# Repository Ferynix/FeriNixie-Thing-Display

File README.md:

# FeriNixie Thing Display
 A nixie tube display for furries ;3

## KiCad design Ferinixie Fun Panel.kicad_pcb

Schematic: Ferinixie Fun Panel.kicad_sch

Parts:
C1, C2: 1uF; C_Radial_D5.0mm_H5.0mm_P2.00mm
C5, C6, C7, C8: 100nF; C_0402_1005Metric
D1: MB6S; TO-269AA
NE1, NE2, NE3, NE4, NE5, NE6, NE7, NE8, NE9, NE10, NE11, NE12, NE13, NE14, NE15, NE16, NE17, NE18: INS-1
NIX1, NIX2, NIX3, NIX4, NIX5, NIX6, NIX7, NIX8, NIX9, NIX10, NIX11, NIX12, NIX13, NIX14, NIX15: IN-15A; IN-15A Stepped
PS1: IRM-05-5; Converter_ACDC_MeanWell_IRM-05-xx_THT
Q1, Q2, Q3, Q4, Q5, Q6, Q7, Q8, Q9, Q10, Q11, Q12, Q13, Q14, Q15, Q16, Q17, Q18, Q19, Q20, Q21, Q22, Q23, Q24, Q25, Q26, Q27, Q28, Q29, Q30, Q31, Q32, Q33, Q34, Q35, Q36, Q37, Q38, Q39, Q40, Q41, Q42, Q43, Q44, Q45, Q46, Q47, Q48, Q49, Q50, Q51, Q52, Q53, Q54, Q55, Q56, Q57, Q58, Q59, Q60, Q61, Q62, Q63, Q64, Q65, Q66, Q67, Q68, Q69, Q70, Q71, Q72, Q73, Q74, Q75, Q76, Q77, Q78, Q79, Q80, Q81, Q82, Q83, Q84, Q85, Q86, Q87, Q88, Q89, Q90, Q91, Q92, Q93, Q94, Q95, Q96, Q97, Q98, Q99, Q100, Q101, Q102, Q103, Q104, Q105, Q106, Q107, Q108, Q109, Q110, Q111, Q112, Q113, Q114, Q115, Q116, Q117, Q118, Q119, Q120, Q121, Q122, Q123, Q124, Q125, Q126, Q127, Q128, Q129, Q130, Q131, Q132, Q133, Q134, Q135, Q136, Q137, Q138, Q139, Q140, Q141, Q142, Q143, Q144, Q145, Q146, Q147, Q148, Q149, Q150, Q151, Q152, Q153, Q154, Q155, Q156, Q157, Q158, Q159, Q160, Q161, Q162, Q163, Q164, Q165, Q166, Q167, Q168: MMBTA42; SOT-23 No Courtyard
R1, R2, R3, R4, R5, R6, R7, R8, R9, R10, R11, R12, R13, R14, R15: 20K; R_1206_3216Metric
R16, R17, R18, R19, R20, R21, R22, R23, R24, R25, R26, R27, R28, R29, R30, R31, R32, R33, R34, R35, R36, R37, R38, R39, R40, R41, R42, R43, R44, R45, R46, R47, R48, R49, R50, R51, R52, R53, R54, R55, R56, R57, R58, R59, R60, R61, R62, R63, R64, R65, R66, R67, R68, R69, R70, R71, R72, R73, R74, R75, R76, R77, R78, R79, R80, R81, R82, R83, R84, R85, R86, R87, R88, R89, R90, R91, R92, R93, R94, R95, R96, R97, R98, R99, R100, R101, R102, R103, R104, R105, R106, R107, R108, R109, R110, R111, R112, R113, R114, R115, R116, R117, R118, R119, R120, R121, R122, R123, R124, R125, R126, R127, R128, R129, R130, R131, R132, R133, R134, R135, R136, R137, R138, R139, R140, R141, R142, R143, R144, R145, R146, R147, R148, R149, R150, R151, R152, R153, R154, R155, R156, R157, R158, R159, R160, R161, R162, R163, R164, R165, R171, R172, R173, R174, R175, R176, R177, R178, R179, R180, R181, R182, R183, R184, R185, R186, R187, R188: 10K; R_0402_1005Metric
R166, R167, R168, R169, R170: 1K; R_0402_1005Metric
R189, R190, R191, R192, R193, R194, R195, R196, R197, R198, R199, R200, R201, R202, R203, R204, R205, R206: 100K; R_1206_3216Metric
U1, U2, U3, U4, U5, U6, U7, U8, U9, U10, U11, U12, U13, U14, U15, U16, U17, U18, U19, U39, U40: 74HC595_Slim; SOIC-16_3.9x9.9mm_P1.27mm
U20: RP2040-Tiny; RP2040-Tiny Package Extra Clearance SMD
U21: JEITA_SOIC-16_3.9x9.9mm_P1.27mm
U24, U25, U26, U27, U28, U29, U30, U31, U32, U33, U34, U35, U36, U37, U38: PinHeader_1x10_P1.00mm_Vertical

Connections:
unnamed: D1.1, PS1.1 (AC/N)
unnamed: D1.2, PS1.2 (AC/L)
unnamed: NE1.1 (A), R189.1
unnamed: NE1.2 (K), Q151.3 (C)
unnamed: NE2.1 (A), R190.1
unnamed: NE2.2 (K), Q152.3 (C)
unnamed: NE3.1 (A), R191.1
unnamed: NE3.2 (K), Q153.3 (C)
unnamed: NE4.1 (A), R192.1
unnamed: NE4.2 (K), Q154.3 (C)
unnamed: NE5.1 (A), R193.1
unnamed: NE5.2 (K), Q155.3 (C)
unnamed: NE6.1 (A), R194.1
unnamed: NE6.2 (K), Q156.3 (C)
unnamed: NE7.1 (A), R195.1
unnamed: NE7.2 (K), Q157.3 (C)
unnamed: NE8.1 (A), R196.1
unnamed: NE8.2 (K), Q158.3 (C)
unnamed: NE9.1 (A), R197.1
unnamed: NE9.2 (K), Q159.3 (C)
unnamed: NE10.1 (A), R198.1
unnamed: NE10.2 (K), Q160.3 (C)
unnamed: NE11.1 (A), R199.1
unnamed: NE11.2 (K), Q161.3 (C)
unnamed: NE12.1 (A), R200.1
unnamed: NE12.2 (K), Q162.3 (C)
unnamed: NE13.1 (A), R201.1
unnamed: NE13.2 (K), Q163.3 (C)
unnamed: NE14.1 (A), R202.1
unnamed: NE14.2 (K), Q164.3 (C)
unnamed: NE15.1 (A), R203.1
unnamed: NE15.2 (K), Q165.3 (C)
unnamed: NE16.1 (A), R204.1
unnamed: NE16.2 (K), Q166.3 (C)
unnamed: NE17.1 (A), R205.1
unnamed: NE17.2 (K), Q167.3 (C)
unnamed: NE18.1 (A), R206.1
unnamed: NE18.2 (K), Q168.3 (C)
unnamed 38: NIX1.10 (%), Q7.3 (C), U24.7; also elsewhere on the board
unnamed 39: NIX1.5 (+), Q4.3 (C), U24.4; also elsewhere on the board
unnamed 40: NIX1.4 (-), Q3.3 (C), U24.3; also elsewhere on the board
unnamed 41: NIX1.7 (M), Q10.3 (C), U24.10; also elsewhere on the board
unnamed 42: NIX1.3, Q2.3 (C), U24.2; also elsewhere on the board
unnamed 43: NIX1.8 (k), Q9.3 (C), U24.9; also elsewhere on the board
unnamed 44: NIX1.6 (m), Q5.3 (C), U24.5; also elsewhere on the board
unnamed 45: NIX1.11 (n), Q6.3 (C), U24.6; also elsewhere on the board
unnamed: NIX1.1 (~A), R1.1
unnamed 47: NIX1.2 (µ), Q1.3 (C), U24.1; also elsewhere on the board
unnamed 48: NIX1.9 (П), Q8.3 (C), U24.8; also elsewhere on the board
unnamed 49: NIX2.10 (%), Q17.3 (C), U25.7; also elsewhere on the board
unnamed 50: NIX2.5 (+), Q14.3 (C), U25.4; also elsewhere on the board
unnamed 51: NIX2.4 (-), Q13.3 (C), U25.3; also elsewhere on the board
unnamed 52: NIX2.7 (M), Q20.3 (C), U25.10; also elsewhere on the board
unnamed 53: NIX2.3, Q12.3 (C), U25.2; also elsewhere on the board
unnamed 54: NIX2.8 (k), Q19.3 (C), U25.9; also elsewhere on the board
unnamed 55: NIX2.6 (m), Q15.3 (C), U25.5; also elsewhere on the board
unnamed 56: NIX2.11 (n), Q16.3 (C), U25.6; also elsewhere on the board
unnamed: NIX2.1 (~A), R2.1
unnamed 58: NIX2.2 (µ), Q11.3 (C), U25.1; also elsewhere on the board
unnamed 59: NIX2.9 (П), Q18.3 (C), U25.8; also elsewhere on the board
unnamed 60: NIX3.10 (%), Q27.3 (C), U26.7; also elsewhere on the board
unnamed 61: NIX3.5 (+), Q24.3 (C), U26.4; also elsewhere on the board
unnamed 62: NIX3.4 (-), Q23.3 (C), U26.3; also elsewhere on the board
unnamed 63: NIX3.7 (M), Q30.3 (C), U26.10; also elsewhere on the board
unnamed 64: NIX3.3, Q22.3 (C), U26.2; also elsewhere on the board
unnamed 65: NIX3.8 (k), Q29.3 (C), U26.9; also elsewhere on the board
unnamed 66: NIX3.6 (m), Q25.3 (C), U26.5; also elsewhere on the board
unnamed 67: NIX3.11 (n), Q26.3 (C), U26.6; also elsewhere on the board
unnamed: NIX3.1 (~A), R3.1
unnamed 69: NIX3.2 (µ), Q21.3 (C), U26.1; also elsewhere on the board
unnamed 70: NIX3.9 (П), Q28.3 (C), U26.8; also elsewhere on the board
unnamed 71: NIX4.10 (%), Q37.3 (C), U27.7; also elsewhere on the board
unnamed 72: NIX4.5 (+), Q34.3 (C), U27.4; also elsewhere on the board
unnamed 73: NIX4.4 (-), Q33.3 (C), U27.3; also elsewhere on the board
unnamed 74: NIX4.7 (M), Q40.3 (C), U27.10; also elsewhere on the board
unnamed 75: NIX4.3, Q32.3 (C), U27.2; also elsewhere on the board
unnamed 76: NIX4.8 (k), Q39.3 (C), U27.9; also elsewhere on the board
unnamed 77: NIX4.6 (m), Q35.3 (C), U27.5; also elsewhere on the board
unnamed 78: NIX4.11 (n), Q36.3 (C), U27.6; also elsewhere on the board
unnamed: NIX4.1 (~A), R4.1
unnamed 80: NIX4.2 (µ), Q31.3 (C), U27.1; also elsewhere on the board
unnamed 81: NIX4.9 (П), Q38.3 (C), U27.8; also elsewhere on the board
unnamed 82: NIX5.10 (%), Q47.3 (C), U28.7; also elsewhere on the board
unnamed 83: NIX5.5 (+), Q44.3 (C), U28.4; also elsewhere on the board
unnamed 84: NIX5.4 (-), Q43.3 (C), U28.3; also elsewhere on the board
unnamed 85: NIX5.7 (M), Q50.3 (C), U28.10; also elsewhere on the board
unnamed 86: NIX5.3, Q42.3 (C), U28.2; also elsewhere on the board
unnamed 87: NIX5.8 (k), Q49.3 (C), U28.9; also elsewhere on the board
unnamed 88: NIX5.6 (m), Q45.3 (C), U28.5; also elsewhere on the board
unnamed 89: NIX5.11 (n), Q46.3 (C), U28.6; also elsewhere on the board
unnamed: NIX5.1 (~A), R5.1
unnamed 91: NIX5.2 (µ), Q41.3 (C), U28.1; also elsewhere on the board
unnamed 92: NIX5.9 (П), Q48.3 (C), U28.8; also elsewhere on the board
unnamed 93: NIX6.10 (%), Q57.3 (C), U29.7; also elsewhere on the board
unnamed 94: NIX6.5 (+), Q54.3 (C), U29.4; also elsewhere on the board
unnamed 95: NIX6.4 (-), Q53.3 (C), U29.3; also elsewhere on the board
unnamed 96: NIX6.7 (M), Q60.3 (C), U29.10; also elsewhere on the board
unnamed 97: NIX6.3, Q52.3 (C), U29.2; also elsewhere on the board
unnamed 98: NIX6.8 (k), Q59.3 (C), U29.9; also elsewhere on the board
unnamed 99: NIX6.6 (m), Q55.3 (C), U29.5; also elsewhere on the board
unnamed 100: NIX6.11 (n), Q56.3 (C), U29.6; also elsewhere on the board
unnamed: NIX6.1 (~A), R6.1
unnamed 102: NIX6.2 (µ), Q51.3 (C), U29.1; also elsewhere on the board
unnamed 103: NIX6.9 (П), Q58.3 (C), U29.8; also elsewhere on the board
unnamed 104: NIX7.10 (%), Q67.3 (C), U30.7; also elsewhere on the board
unnamed 105: NIX7.5 (+), Q64.3 (C), U30.4; also elsewhere on the board
unnamed 106: NIX7.4 (-), Q63.3 (C), U30.3; also elsewhere on the board
unnamed 107: NIX7.7 (M), Q70.3 (C), U30.10; also elsewhere on the board
unnamed 108: NIX7.3, Q62.3 (C), U30.2; also elsewhere on the board
unnamed 109: NIX7.8 (k), Q69.3 (C), U30.9; also elsewhere on the board
unnamed 110: NIX7.6 (m), Q65.3 (C), U30.5; also elsewhere on the board
unnamed 111: NIX7.11 (n), Q66.3 (C), U30.6; also elsewhere on the board
unnamed: NIX7.1 (~A), R7.1
unnamed 113: NIX7.2 (µ), Q61.3 (C), U30.1; also elsewhere on the board
unnamed 114: NIX7.9 (П), Q68.3 (C), U30.8; also elsewhere on the board
unnamed 115: NIX8.10 (%), Q77.3 (C), U31.7; also elsewhere on the board
unnamed 116: NIX8.5 (+), Q74.3 (C), U31.4; also elsewhere on the board
unnamed 117: NIX8.4 (-), Q73.3 (C), U31.3; also elsewhere on the board
unnamed 118: NIX8.7 (M), Q80.3 (C), U31.10; also elsewhere on the board
unnamed 119: NIX8.3, Q72.3 (C), U31.2; also elsewhere on the board
unnamed 120: NIX8.8 (k), Q79.3 (C), U31.9; also elsewhere on the board
unnamed 121: NIX8.6 (m), Q75.3 (C), U31.5; also elsewhere on the board
unnamed 122: NIX8.11 (n), Q76.3 (C), U31.6; also elsewhere on the board
unnamed: NIX8.1 (~A), R8.1
unnamed 124: NIX8.2 (µ), Q71.3 (C), U31.1; also elsewhere on the board
unnamed 125: NIX8.9 (П), Q78.3 (C), U31.8; also elsewhere on the board
unnamed 126: NIX9.10 (%), Q87.3 (C), U32.7; also elsewhere on the board
unnamed 127: NIX9.5 (+), Q84.3 (C), U32.4; also elsewhere on the board
unnamed 128: NIX9.4 (-), Q83.3 (C), U32.3; also elsewhere on the board
unnamed 129: NIX9.7 (M), Q90.3 (C), U32.10; also elsewhere on the board
unnamed 130: NIX9.3, Q82.3 (C), U32.2; also elsewhere on the board
unnamed 131: NIX9.8 (k), Q89.3 (C), U32.9; also elsewhere on the board
unnamed 132: NIX9.6 (m), Q85.3 (C), U32.5; also elsewhere on the board
unnamed 133: NIX9.11 (n), Q86.3 (C), U32.6; also elsewhere on the board
unnamed: NIX9.1 (~A), R9.1
unnamed 135: NIX9.2 (µ), Q81.3 (C), U32.1; also elsewhere on the board
unnamed 136: NIX9.9 (П), Q88.3 (C), U32.8; also elsewhere on the board
unnamed 137: NIX10.10 (%), Q97.3 (C), U33.7; also elsewhere on the board
unnamed 138: NIX10.5 (+), Q94.3 (C), U33.4; also elsewhere on the board
unnamed 139: NIX10.4 (-), Q93.3 (C), U33.3; also elsewhere on the board
unnamed 140: NIX10.7 (M), Q100.3 (C), U33.10; also elsewhere on the board
unnamed 141: NIX10.3, Q92.3 (C), U33.2; also elsewhere on the board
unnamed 142: NIX10.8 (k), Q99.3 (C), U33.9; also elsewhere on the board
unnamed 143: NIX10.6 (m), Q95.3 (C), U33.5; also elsewhere on the board
unnamed 144: NIX10.11 (n), Q96.3 (C), U33.6; also elsewhere on the board
unnamed: NIX10.1 (~A), R10.1
unnamed 146: NIX10.2 (µ), Q91.3 (C), U33.1; also elsewhere on the board
unnamed 147: NIX10.9 (П), Q98.3 (C), U33.8; also elsewhere on the board
unnamed 148: NIX11.10 (%), Q107.3 (C), U34.7; also elsewhere on the board
unnamed 149: NIX11.5 (+), Q104.3 (C), U34.4; also elsewhere on the board
unnamed 150: NIX11.4 (-), Q103.3 (C), U34.3; also elsewhere on the board
unnamed 151: NIX11.7 (M), Q110.3 (C), U34.10; also elsewhere on the board
unnamed 152: NIX11.3, Q102.3 (C), U34.2; also elsewhere on the board
unnamed 153: NIX11.8 (k), Q109.3 (C), U34.9; also elsewhere on the board
unnamed 154: NIX11.6 (m), Q105.3 (C), U34.5; also elsewhere on the board
unnamed 155: NIX11.11 (n), Q106.3 (C), U34.6; also elsewhere on the board
unnamed: NIX11.1 (~A), R11.1
unnamed 157: NIX11.2 (µ), Q101.3 (C), U34.1; also elsewhere on the board
unnamed 158: NIX11.9 (П), Q108.3 (C), U34.8; also elsewhere on the board
unnamed 159: NIX12.10 (%), Q117.3 (C), U35.7; also elsewhere on the board
unnamed 160: NIX12.5 (+), Q114.3 (C), U35.4; also elsewhere on the board
unnamed 161: NIX12.4 (-), Q113.3 (C), U35.3; also elsewhere on the board
unnamed 162: NIX12.7 (M), Q120.3 (C), U35.10; also elsewhere on the board
unnamed 163: NIX12.3, Q112.3 (C), U35.2; also elsewhere on the board
unnamed 164: NIX12.8 (k), Q119.3 (C), U35.9; also elsewhere on the board
unnamed 165: NIX12.6 (m), Q115.3 (C), U35.5; also elsewhere on the board
unnamed 166: NIX12.11 (n), Q116.3 (C), U35.6; also elsewhere on the board
unnamed: NIX12.1 (~A), R12.1
unnamed 168: NIX12.2 (µ), Q111.3 (C), U35.1; also elsewhere on the board
unnamed 169: NIX12.9 (П), Q118.3 (C), U35.8; also elsewhere on the board
unnamed 170: NIX13.10 (%), Q127.3 (C), U36.7; also elsewhere on the board
unnamed 171: NIX13.5 (+), Q124.3 (C), U36.4; also elsewhere on the board
unnamed 172: NIX13.4 (-), Q123.3 (C), U36.3; also elsewhere on the board
unnamed 173: NIX13.7 (M), Q130.3 (C), U36.10; also elsewhere on the board
unnamed 174: NIX13.3, Q122.3 (C), U36.2; also elsewhere on the board
unnamed 175: NIX13.8 (k), Q129.3 (C), U36.9; also elsewhere on the board
unnamed 176: NIX13.6 (m), Q125.3 (C), U36.5; also elsewhere on the board
unnamed 177: NIX13.11 (n), Q126.3 (C), U36.6; also elsewhere on the board
unnamed: NIX13.1 (~A), R13.1
unnamed 179: NIX13.2 (µ), Q121.3 (C), U36.1; also elsewhere on the board
unnamed 180: NIX13.9 (П), Q128.3 (C), U36.8; also elsewhere on the board
unnamed 181: NIX14.10 (%), Q137.3 (C), U37.7; also elsewhere on the board
unnamed 182: NIX14.5 (+), Q134.3 (C), U37.4; also elsewhere on the board
unnamed 183: NIX14.4 (-), Q133.3 (C), U37.3; also elsewhere on the board
unnamed 184: NIX14.7 (M), Q140.3 (C), U37.10; also elsewhere on the board
unnamed 185: NIX14.3, Q132.3 (C), U37.2; also elsewhere on the board
unnamed 186: NIX14.8 (k), Q139.3 (C), U37.9; also elsewhere on the board
unnamed 187: NIX14.6 (m), Q135.3 (C), U37.5; also elsewhere on the board
unnamed 188: NIX14.11 (n), Q136.3 (C), U37.6; also elsewhere on the board
unnamed: NIX14.1 (~A), R14.1
unnamed 190: NIX14.2 (µ), Q131.3 (C), U37.1; also elsewhere on the board
unnamed 191: NIX14.9 (П), Q138.3 (C), U37.8; also elsewhere on the board
unnamed 192: NIX15.10 (%), Q147.3 (C), U38.7; also elsewhere on the board
unnamed 193: NIX15.5 (+), Q144.3 (C), U38.4; also elsewhere on the board
unnamed 194: NIX15.4 (-), Q143.3 (C), U38.3; also elsewhere on the board
unnamed 195: NIX15.7 (M), Q150.3 (C), U38.10; also elsewhere on the board
unnamed 196: NIX15.3, Q142.3 (C), U38.2; also elsewhere on the board
unnamed 197: NIX15.8 (k), Q149.3 (C), U38.9; also elsewhere on the board
unnamed 198: NIX15.6 (m), Q145.3 (C), U38.5; also elsewhere on the board
unnamed 199: NIX15.11 (n), Q146.3 (C), U38.6; also elsewhere on the board
unnamed: NIX15.1 (~A), R15.1
unnamed 201: NIX15.2 (µ), Q141.3 (C), U38.1; also elsewhere on the board
unnamed 202: NIX15.9 (П), Q148.3 (C), U38.8; also elsewhere on the board
unnamed: Q1.1 (B), R16.2
unnamed: Q2.1 (B), R17.2
unnamed: Q3.1 (B), R18.2
unnamed: Q4.1 (B), R19.2
unnamed: Q5.1 (B), R20.2
unnamed: Q6.1 (B), R21.2
unnamed: Q7.1 (B), R22.2
unnamed: Q8.1 (B), R23.2
unnamed: Q9.1 (B), R24.2
unnamed: Q10.1 (B), R25.2
unnamed: Q11.1 (B), R26.2
unnamed: Q12.1 (B), R27.2
unnamed: Q13.1 (B), R28.2
unnamed: Q14.1 (B), R29.2
unnamed: Q15.1 (B), R30.2
unnamed: Q16.1 (B), R31.2
unnamed: Q17.1 (B), R32.2
unnamed: Q18.1 (B), R33.2
unnamed: Q19.1 (B), R34.2
unnamed: Q20.1 (B), R35.2
unnamed: Q21.1 (B), R36.2
unnamed: Q22.1 (B), R37.2
unnamed: Q23.1 (B), R38.2
unnamed: Q24.1 (B), R39.2
unnamed: Q25.1 (B), R40.2
unnamed: Q26.1 (B), R41.2
unnamed: Q27.1 (B), R42.2
unnamed: Q28.1 (B), R43.2
unnamed: Q29.1 (B), R44.2
unnamed: Q30.1 (B), R45.2
unnamed: Q31.1 (B), R46.2
unnamed: Q32.1 (B), R47.2
unnamed: Q33.1 (B), R48.2
unnamed: Q34.1 (B), R49.2
unnamed: Q35.1 (B), R50.2
unnamed: Q36.1 (B), R51.2
unnamed: Q37.1 (B), R52.2
unnamed: Q38.1 (B), R53.2
unnamed: Q39.1 (B), R54.2
unnamed: Q40.1 (B), R55.2
unnamed: Q41.1 (B), R56.2
unnamed: Q42.1 (B), R57.2
unnamed: Q43.1 (B), R58.2
unnamed: Q44.1 (B), R59.2
unnamed: Q45.1 (B), R60.2
unnamed: Q46.1 (B), R61.2
unnamed: Q47.1 (B), R62.2
unnamed: Q48.1 (B), R63.2
unnamed: Q49.1 (B), R64.2
unnamed: Q50.1 (B), R65.2
unnamed: Q51.1 (B), R66.2
unnamed: Q52.1 (B), R67.2
unnamed: Q53.1 (B), R68.2
unnamed: Q54.1 (B), R69.2
unnamed: Q55.1 (B), R70.2
unnamed: Q56.1 (B), R71.2
unnamed: Q57.1 (B), R72.2
unnamed: Q58.1 (B), R73.2
unnamed: Q59.1 (B), R74.2
unnamed: Q60.1 (B), R75.2
unnamed: Q61.1 (B), R76.2
unnamed: Q62.1 (B), R77.2
unnamed: Q63.1 (B), R78.2
unnamed: Q64.1 (B), R79.2
unnamed: Q65.1 (B), R80.2
unnamed: Q66.1 (B), R81.2
unnamed: Q67.1 (B), R82.2
unnamed: Q68.1 (B), R83.2
unnamed: Q69.1 (B), R84.2
unnamed: Q70.1 (B), R85.2
unnamed: Q71.1 (B), R86.2
unnamed: Q72.1 (B), R87.2
unnamed: Q73.1 (B), R88.2
unnamed: Q74.1 (B), R89.2
unnamed: Q75.1 (B), R90.2
unnamed: Q76.1 (B), R91.2
unnamed: Q77.1 (B), R92.2
unnamed: Q78.1 (B), R93.2
unnamed: Q79.1 (B), R94.2
unnamed: Q80.1 (B), R95.2
unnamed: Q81.1 (B), R96.2
unnamed: Q82.1 (B), R97.2
unnamed: Q83.1 (B), R98.2
unnamed: Q84.1 (B), R99.2
unnamed: Q85.1 (B), R100.2
unnamed: Q86.1 (B), R101.2
unnamed: Q87.1 (B), R102.2
unnamed: Q88.1 (B), R103.2
unnamed: Q89.1 (B), R104.2
unnamed: Q90.1 (B), R105.2
unnamed: Q91.1 (B), R106.2
unnamed: Q92.1 (B), R107.2
unnamed: Q93.1 (B), R108.2
unnamed: Q94.1 (B), R109.2
unnamed: Q95.1 (B), R110.2
unnamed: Q96.1 (B), R111.2
unnamed: Q97.1 (B), R112.2
unnamed: Q98.1 (B), R113.2
unnamed: Q99.1 (B), R114.2
unnamed: Q100.1 (B), R115.2
unnamed: Q101.1 (B), R116.2
unnamed: Q102.1 (B), R117.2
unnamed: Q103.1 (B), R118.2
unnamed: Q104.1 (B), R119.2
unnamed: Q105.1 (B), R120.2
unnamed: Q106.1 (B), R121.2
unnamed: Q107.1 (B), R122.2
unnamed: Q108.1 (B), R123.2
unnamed: Q109.1 (B), R124.2
unnamed: Q110.1 (B), R125.2
unnamed: Q111.1 (B), R126.2
unnamed: Q112.1 (B), R127.2
unnamed: Q113.1 (B), R128.2
unnamed: Q114.1 (B), R129.2
unnamed: Q115.1 (B), R130.2
unnamed: Q116.1 (B), R131.2
unnamed: Q117.1 (B), R132.2
unnamed: Q118.1 (B), R133.2
unnamed: Q119.1 (B), R134.2
unnamed: Q120.1 (B), R135.2
unnamed: Q121.1 (B), R136.2
unnamed: Q122.1 (B), R137.2
unnamed: Q123.1 (B), R138.2
unnamed: Q124.1 (B), R139.2
unnamed: Q125.1 (B), R140.2
unnamed: Q126.1 (B), R141.2
unnamed: Q127.1 (B), R142.2
unnamed: Q128.1 (B), R143.2
unnamed: Q129.1 (B), R144.2
unnamed: Q130.1 (B), R145.2
unnamed: Q131.1 (B), R146.2
unnamed: Q132.1 (B), R147.2
unnamed: Q133.1 (B), R148.2
unnamed: Q134.1 (B), R149.2
unnamed: Q135.1 (B), R150.2
unnamed: Q136.1 (B), R151.2
unnamed: Q137.1 (B), R152.2
unnamed: Q138.1 (B), R153.2
unnamed: Q139.1 (B), R154.2
unnamed: Q140.1 (B), R155.2
unnamed: Q141.1 (B), R156.2
unnamed: Q142.1 (B), R157.2
unnamed: Q143.1 (B), R158.2
unnamed: Q144.1 (B), R159.2
unnamed: Q145.1 (B), R160.2
unnamed: Q146.1 (B), R161.2
unnamed: Q147.1 (B), R162.2
unnamed: Q148.1 (B), R163.2
unnamed: Q149.1 (B), R164.2
unnamed: Q150.1 (B), R165.2
unnamed: Q151.1 (B), R171.2
unnamed: Q152.1 (B), R172.2
unnamed: Q153.1 (B), R173.2
unnamed: Q154.1 (B), R174.2
unnamed: Q155.1 (B), R175.2
unnamed: Q156.1 (B), R176.2
unnamed: Q157.1 (B), R177.2
unnamed: Q158.1 (B), R178.2
unnamed: Q159.1 (B), R179.2
unnamed: Q160.1 (B), R180.2
unnamed: Q161.1 (B), R181.2
unnamed: Q162.1 (B), R182.2
unnamed: Q163.1 (B), R183.2
unnamed: Q164.1 (B), R184.2
unnamed: Q165.1 (B), R185.2
unnamed: Q166.1 (B), R186.2
unnamed: Q167.1 (B), R187.2
unnamed: Q168.1 (B), R188.2
unnamed: R16.1, U1.15 (QA)
unnamed: R17.1, U1.1 (QB)
unnamed: R18.1, U1.2 (QC)
unnamed: R19.1, U1.3 (QD)
unnamed: R20.1, U1.4 (QE)
unnamed: R21.1, U1.5 (QF)
unnamed: R22.1, U1.6 (QG)
unnamed: U1.9 (QH'), U2.14 (SER)
unnamed: R23.1, U1.7 (QH)
unnamed: R166.2, U1.14 (SER), U21.2 (INA), U21.15 (OUTA)
unnamed: R24.1, U2.15 (QA)
unnamed: R25.1, U2.1 (QB)
unnamed: R26.1, U2.2 (QC)
unnamed: R27.1, U2.3 (QD)
unnamed: R28.1, U2.4 (QE)
unnamed: R29.1, U2.5 (QF)
unnamed: R30.1, U2.6 (QG)
unnamed: U2.9 (QH'), U3.14 (SER)
unnamed: R31.1, U2.7 (QH)
unnamed: R32.1, U3.15 (QA)
unnamed: R33.1, U3.1 (QB)
unnamed: R34.1, U3.2 (QC)
unnamed: R35.1, U3.3 (QD)
unnamed: R36.1, U3.4 (QE)
unnamed: R37.1, U3.5 (QF)
unnamed: R38.1, U3.6 (QG)
unnamed: U3.9 (QH'), U4.14 (SER)
unnamed: R39.1, U3.7 (QH)
unnamed: R40.1, U4.15 (QA)
unnamed: R41.1, U4.1 (QB)
unnamed: R42.1, U4.2 (QC)
unnamed: R43.1, U4.3 (QD)
unnamed: R44.1, U4.4 (QE)
unnamed: R45.1, U4.5 (QF)
unnamed: R46.1, U4.6 (QG)
unnamed: U4.9 (QH'), U5.14 (SER)
unnamed: R47.1, U4.7 (QH)
unnamed: R48.1, U5.15 (QA)
unnamed: R49.1, U5.1 (QB)
unnamed: R50.1, U5.2 (QC)
unnamed: R51.1, U5.3 (QD)
unnamed: R52.1, U5.4 (QE)
unnamed: R53.1, U5.5 (QF)
unnamed: R54.1, U5.6 (QG)
unnamed: U5.9 (QH'), U6.14 (SER)
unnamed: R55.1, U5.7 (QH)
unnamed: R56.1, U6.15 (QA)
unnamed: R57.1, U6.1 (QB)
unnamed: R58.1, U6.2 (QC)
unnamed: R59.1, U6.3 (QD)
unnamed: R60.1, U6.4 (QE)
unnamed: R61.1, U6.5 (QF)
unnamed: R62.1, U6.6 (QG)
unnamed: U6.9 (QH'), U7.14 (SER)
unnamed: R63.1, U6.7 (QH)
unnamed: R64.1, U7.15 (QA)
unnamed: R65.1, U7.1 (QB)
unnamed: R66.1, U7.2 (QC)
unnamed: R67.1, U7.3 (QD)
unnamed: R68.1, U7.4 (QE)
unnamed: R69.1, U7.5 (QF)
unnamed: R70.1, U7.6 (QG)
unnamed: U7.9 (QH'), U8.14 (SER)
unnamed: R71.1, U7.7 (QH)
unnamed: R72.1, U8.15 (QA)
unnamed: R73.1, U8.1 (QB)
unnamed: R74.1, U8.2 (QC)
unnamed: R75.1, U8.3 (QD)
unnamed: R76.1, U8.4 (QE)
unnamed: R77.1, U8.5 (QF)
unnamed: R78.1, U8.6 (QG)
unnamed: U8.9 (QH'), U9.14 (SER)
unnamed: R79.1, U8.7 (QH)
unnamed: R80.1, U9.15 (QA)
unnamed: R81.1, U9.1 (QB)
unnamed: R82.1, U9.2 (QC)
unnamed: R83.1, U9.3 (QD)
unnamed: R84.1, U9.4 (QE)
unnamed: R85.1, U9.5 (QF)
unnamed: R86.1, U9.6 (QG)
unnamed: R87.1, U9.7 (QH)
unnamed: R88.1, U10.15 (QA)
unnamed: R89.1, U10.1 (QB)
unnamed: R90.1, U10.2 (QC)
unnamed: R91.1, U10.3 (QD)
unnamed: R92.1, U10.4 (QE)
unnamed: R93.1, U10.5 (QF)
unnamed: R94.1, U10.6 (QG)
unnamed: U10.9 (QH'), U11.14 (SER)
unnamed: R95.1, U10.7 (QH)
unnamed: U9.9 (QH'), U10.14 (SER)
unnamed: R96.1, U11.15 (QA)
unnamed: R97.1, U11.1 (QB)
unnamed: R98.1, U11.2 (QC)
unnamed: R99.1, U11.3 (QD)
unnamed: R100.1, U11.4 (QE)
unnamed: R101.1, U11.5 (QF)
unnamed: R102.1, U11.6 (QG)
unnamed: U11.9 (QH'), U12.14 (SER)
unnamed: R103.1, U11.7 (QH)
unnamed: U11.16 (VCC), U12.16 (VCC), U13.16 (VCC), U15.16 (VCC)
unnamed: R104.1, U12.15 (QA)
unnamed: R105.1, U12.1 (QB)
unnamed: R106.1, U12.2 (QC)
unnamed: R107.1, U12.3 (QD)
unnamed: R108.1, U12.4 (QE)
unnamed: R109.1, U12.5 (QF)
unnamed: R110.1, U12.6 (QG)
unnamed: U12.9 (QH'), U13.14 (SER)
unnamed: R111.1, U12.7 (QH)
unnamed: R112.1, U13.15 (QA)
unnamed: R113.1, U13.1 (QB)
unnamed: R114.1, U13.2 (QC)
unnamed: R115.1, U13.3 (QD)
unnamed: R116.1, U13.4 (QE)
unnamed: R117.1, U13.5 (QF)
unnamed: R118.1, U13.6 (QG)
unnamed: U13.9 (QH'), U14.14 (SER)
unnamed: R119.1, U13.7 (QH)
unnamed: R120.1, U14.15 (QA)
unnamed: R121.1, U14.1 (QB)
unnamed: R122.1, U14.2 (QC)
unnamed: R123.1, U14.3 (QD)
unnamed: R124.1, U14.4 (QE)
unnamed: R125.1, U14.5 (QF)
unnamed: R126.1, U14.6 (QG)
unnamed: U14.9 (QH'), U15.14 (SER)
unnamed: R127.1, U14.7 (QH)
unnamed: R128.1, U15.15 (QA)
unnamed: R129.1, U15.1 (QB)
unnamed: R130.1, U15.2 (QC)
unnamed: R131.1, U15.3 (QD)
unnamed: R132.1, U15.4 (QE)
unnamed: R133.1, U15.5 (QF)
unnamed: R134.1, U15.6 (QG)
unnamed: U15.9 (QH'), U16.14 (SER)
unnamed: R135.1, U15.7 (QH)
unnamed: R136.1, U16.15 (QA)
unnamed: R137.1, U16.1 (QB)
unnamed: R138.1, U16.2 (QC)
unnamed: R139.1, U16.3 (QD)
unnamed: R140.1, U16.4 (QE)
unnamed: R141.1, U16.5 (QF)
unnamed: R142.1, U16.6 (QG)
unnamed: U16.9 (QH'), U17.14 (SER)
unnamed: R143.1, U16.7 (QH)
unnamed: R144.1, U17.15 (QA)
unnamed: R145.1, U17.1 (QB)
unnamed: R146.1, U17.2 (QC)
unnamed: R147.1, U17.3 (QD)
unnamed: R148.1, U17.4 (QE)
unnamed: R149.1, U17.5 (QF)
unnamed: R150.1, U17.6 (QG)
unnamed: U17.9 (QH'), U18.14 (SER)
unnamed: R151.1, U17.7 (QH)
unnamed: R152.1, U18.15 (QA)
unnamed: R153.1, U18.1 (QB)
unnamed: R154.1, U18.2 (QC)
unnamed: R155.1, U18.3 (QD)
unnamed: R156.1, U18.4 (QE)
unnamed: R157.1, U18.5 (QF)
unnamed: R158.1, U18.6 (QG)
unnamed: U18.9 (QH'), U19.14 (SER)
unnamed: R159.1, U18.7 (QH)
unnamed: R160.1, U19.15 (QA)
unnamed: R161.1, U19.1 (QB)
unnamed: R162.1, U19.2 (QC)
unnamed: R163.1, U19.3 (QD)
unnamed: R164.1, U19.4 (QE)
unnamed: R165.1, U19.5 (QF)
unnamed: R171.1, U19.6 (QG)
unnamed: U19.9 (QH'), U39.14 (SER)
unnamed: R172.1, U19.7 (QH)
unnamed: R166.1, U20.23 (0)
unnamed: R167.1, U20.22 (1)
unnamed: R168.1, U20.21 (2)
unnamed: R169.1, U20.20 (3)
unnamed: R170.1, U20.19 (4)
unnamed: U20.3 (+3V3), U21.1 (VDD1)
unnamed: R173.1, U39.15 (QA)
unnamed: R174.1, U39.1 (QB)
unnamed: R175.1, U39.2 (QC)
unnamed: R176.1, U39.3 (QD)
unnamed: R177.1, U39.4 (QE)
unnamed: R178.1, U39.5 (QF)
unnamed: R179.1, U39.6 (QG)
unnamed: U39.9 (QH'), U40.14 (SER)
unnamed: R180.1, U39.7 (QH)
unnamed: R181.1, U40.15 (QA)
unnamed: R182.1, U40.1 (QB)
unnamed: R183.1, U40.2 (QC)
unnamed: R184.1, U40.3 (QD)
unnamed: R185.1, U40.4 (QE)
unnamed: R186.1, U40.5 (QF)
unnamed: R187.1, U40.6 (QG)
unnamed: R188.1, U40.7 (QH)

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
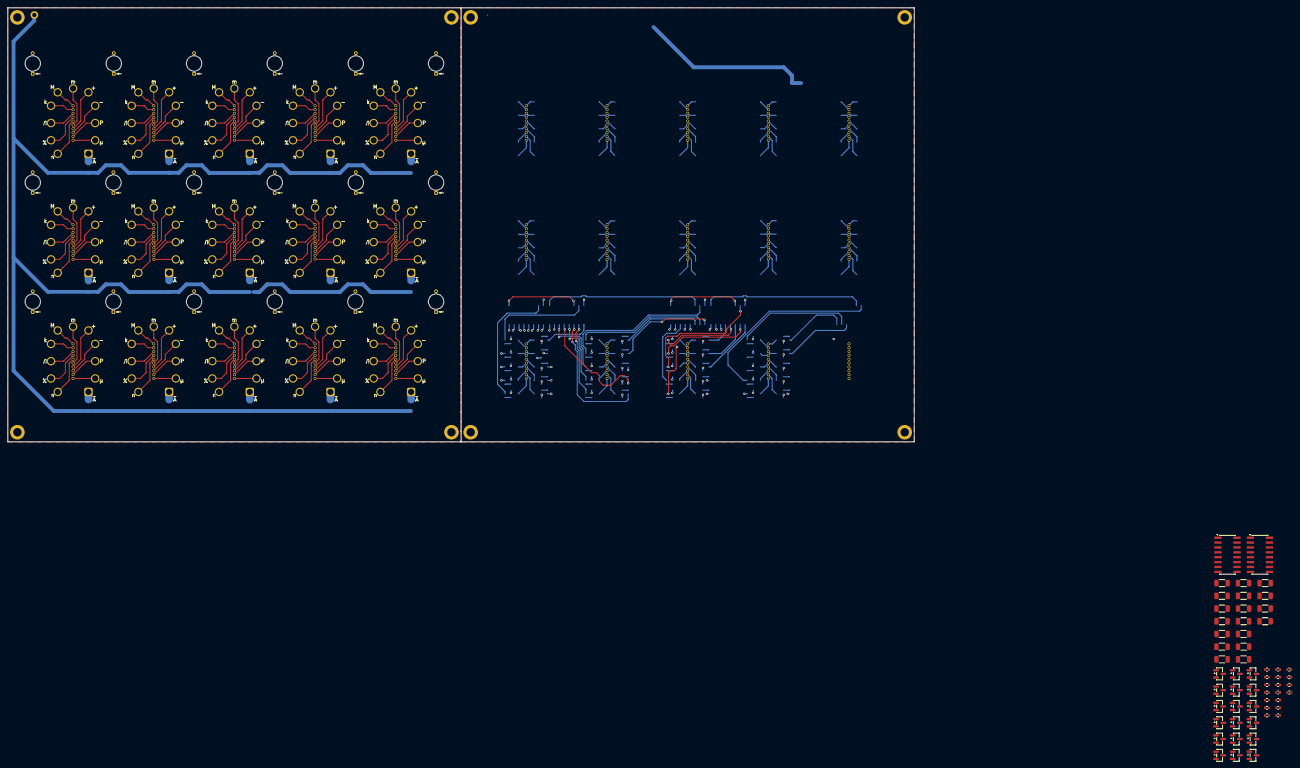
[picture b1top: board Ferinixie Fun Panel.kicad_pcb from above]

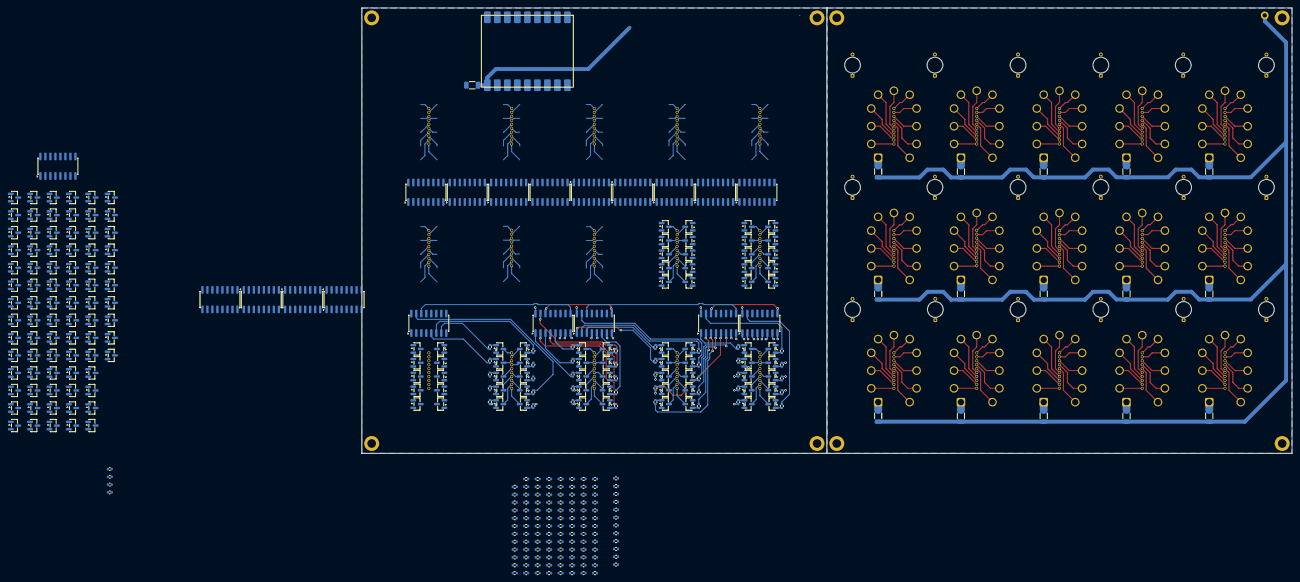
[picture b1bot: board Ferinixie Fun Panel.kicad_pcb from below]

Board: 4 copper layers, 236.0 x 113.0 mm, 464 parts (345 on the bottom side), 572 nets.

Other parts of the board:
U24#2, U25#2, U26#2, U27#2, U28#2, U29#2, U30#2, U31#2, U32#2, U33#2, U34#2, U35#2, U36#2, U37#2, U38#2: PinHeader_1x10_P1.00mm_Vertical

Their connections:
unnamed 38: U24#2.7; also elsewhere on the board
unnamed 39: U24#2.4; also elsewhere on the board
unnamed 40: U24#2.3; also elsewhere on the board
unnamed 41: U24#2.10; also elsewhere on the board
unnamed 42: U24#2.2; also elsewhere on the board
unnamed 43: U24#2.9; also elsewhere on the board
unnamed 44: U24#2.5; also elsewhere on the board
unnamed 45: U24#2.6; also elsewhere on the board
unnamed 47: U24#2.1; also elsewhere on the board
unnamed 48: U24#2.8; also elsewhere on the board
unnamed 49: U25#2.7; also elsewhere on the board
unnamed 50: U25#2.4; also elsewhere on the board
unnamed 51: U25#2.3; also elsewhere on the board
unnamed 52: U25#2.10; also elsewhere on the board
unnamed 53: U25#2.2; also elsewhere on the board
unnamed 54: U25#2.9; also elsewhere on the board
unnamed 55: U25#2.5; also elsewhere on the board
unnamed 56: U25#2.6; also elsewhere on the board
unnamed 58: U25#2.1; also elsewhere on the board
unnamed 59: U25#2.8; also elsewhere on the board
unnamed 60: U26#2.7; also elsewhere on the board
unnamed 61: U26#2.4; also elsewhere on the board
unnamed 62: U26#2.3; also elsewhere on the board
unnamed 63: U26#2.10; also elsewhere on the board
unnamed 64: U26#2.2; also elsewhere on the board
unnamed 65: U26#2.9; also elsewhere on the board
unnamed 66: U26#2.5; also elsewhere on the board
unnamed 67: U26#2.6; also elsewhere on the board
unnamed 69: U26#2.1; also elsewhere on the board
unnamed 70: U26#2.8; also elsewhere on the board
unnamed 71: U27#2.7; also elsewhere on the board
unnamed 72: U27#2.4; also elsewhere on the board
unnamed 73: U27#2.3; also elsewhere on the board
unnamed 74: U27#2.10; also elsewhere on the board
unnamed 75: U27#2.2; also elsewhere on the board
unnamed 76: U27#2.9; also elsewhere on the board
unnamed 77: U27#2.5; also elsewhere on the board
unnamed 78: U27#2.6; also elsewhere on the board
unnamed 80: U27#2.1; also elsewhere on the board
unnamed 81: U27#2.8; also elsewhere on the board
unnamed 82: U28#2.7; also elsewhere on the board
unnamed 83: U28#2.4; also elsewhere on the board
unnamed 84: U28#2.3; also elsewhere on the board
unnamed 85: U28#2.10; also elsewhere on the board
unnamed 86: U28#2.2; also elsewhere on the board
unnamed 87: U28#2.9; also elsewhere on the board
unnamed 88: U28#2.5; also elsewhere on the board
unnamed 89: U28#2.6; also elsewhere on the board
unnamed 91: U28#2.1; also elsewhere on the board
unnamed 92: U28#2.8; also elsewhere on the board
unnamed 93: U29#2.7; also elsewhere on the board
unnamed 94: U29#2.4; also elsewhere on the board
unnamed 95: U29#2.3; also elsewhere on the board
unnamed 96: U29#2.10; also elsewhere on the board
unnamed 97: U29#2.2; also elsewhere on the board
unnamed 98: U29#2.9; also elsewhere on the board
unnamed 99: U29#2.5; also elsewhere on the board
unnamed 100: U29#2.6; also elsewhere on the board
unnamed 102: U29#2.1; also elsewhere on the board
unnamed 103: U29#2.8; also elsewhere on the board
unnamed 104: U30#2.7; also elsewhere on the board
unnamed 105: U30#2.4; also elsewhere on the board
unnamed 106: U30#2.3; also elsewhere on the board
unnamed 107: U30#2.10; also elsewhere on the board
unnamed 108: U30#2.2; also elsewhere on the board
unnamed 109: U30#2.9; also elsewhere on the board
unnamed 110: U30#2.5; also elsewhere on the board
unnamed 111: U30#2.6; also elsewhere on the board
unnamed 113: U30#2.1; also elsewhere on the board
unnamed 114: U30#2.8; also elsewhere on the board
unnamed 115: U31#2.7; also elsewhere on the board
unnamed 116: U31#2.4; also elsewhere on the board
unnamed 117: U31#2.3; also elsewhere on the board
unnamed 118: U31#2.10; also elsewhere on the board
unnamed 119: U31#2.2; also elsewhere on the board
unnamed 120: U31#2.9; also elsewhere on the board
unnamed 121: U31#2.5; also elsewhere on the board
unnamed 122: U31#2.6; also elsewhere on the board
unnamed 124: U31#2.1; also elsewhere on the board
unnamed 125: U31#2.8; also elsewhere on the board
unnamed 126: U32#2.7; also elsewhere on the board
unnamed 127: U32#2.4; also elsewhere on the board
unnamed 128: U32#2.3; also elsewhere on the board
unnamed 129: U32#2.10; also elsewhere on the board
unnamed 130: U32#2.2; also elsewhere on the board
unnamed 131: U32#2.9; also elsewhere on the board
unnamed 132: U32#2.5; also elsewhere on the board
unnamed 133: U32#2.6; also elsewhere on the board
unnamed 135: U32#2.1; also elsewhere on the board
unnamed 136: U32#2.8; also elsewhere on the board
unnamed 137: U33#2.7; also elsewhere on the board
unnamed 138: U33#2.4; also elsewhere on the board
unnamed 139: U33#2.3; also elsewhere on the board
unnamed 140: U33#2.10; also elsewhere on the board
unnamed 141: U33#2.2; also elsewhere on the board
unnamed 142: U33#2.9; also elsewhere on the board
unnamed 143: U33#2.5; also elsewhere on the board
unnamed 144: U33#2.6; also elsewhere on the board
unnamed 146: U33#2.1; also elsewhere on the board
unnamed 147: U33#2.8; also elsewhere on the board
unnamed 148: U34#2.7; also elsewhere on the board
unnamed 149: U34#2.4; also elsewhere on the board
unnamed 150: U34#2.3; also elsewhere on the board
unnamed 151: U34#2.10; also elsewhere on the board
unnamed 152: U34#2.2; also elsewhere on the board
unnamed 153: U34#2.9; also elsewhere on the board
unnamed 154: U34#2.5; also elsewhere on the board
unnamed 155: U34#2.6; also elsewhere on the board
unnamed 157: U34#2.1; also elsewhere on the board
unnamed 158: U34#2.8; also elsewhere on the board
unnamed 159: U35#2.7; also elsewhere on the board
unnamed 160: U35#2.4; also elsewhere on the board
unnamed 161: U35#2.3; also elsewhere on the board
unnamed 162: U35#2.10; also elsewhere on the board
unnamed 163: U35#2.2; also elsewhere on the board
unnamed 164: U35#2.9; also elsewhere on the board
unnamed 165: U35#2.5; also elsewhere on the board
unnamed 166: U35#2.6; also elsewhere on the board
unnamed 168: U35#2.1; also elsewhere on the board
unnamed 169: U35#2.8; also elsewhere on the board
unnamed 170: U36#2.7; also elsewhere on the board
unnamed 171: U36#2.4; also elsewhere on the board
unnamed 172: U36#2.3; also elsewhere on the board
unnamed 173: U36#2.10; also elsewhere on the board
unnamed 174: U36#2.2; also elsewhere on the board
unnamed 175: U36#2.9; also elsewhere on the board
unnamed 176: U36#2.5; also elsewhere on the board
unnamed 177: U36#2.6; also elsewhere on the board
unnamed 179: U36#2.1; also elsewhere on the board
unnamed 180: U36#2.8; also elsewhere on the board
unnamed 181: U37#2.7; also elsewhere on the board
unnamed 182: U37#2.4; also elsewhere on the board
unnamed 183: U37#2.3; also elsewhere on the board
unnamed 184: U37#2.10; also elsewhere on the board
unnamed 185: U37#2.2; also elsewhere on the board
unnamed 186: U37#2.9; also elsewhere on the board
unnamed 187: U37#2.5; also elsewhere on the board
unnamed 188: U37#2.6; also elsewhere on the board
unnamed 190: U37#2.1; also elsewhere on the board
unnamed 191: U37#2.8; also elsewhere on the board
unnamed 192: U38#2.7; also elsewhere on the board
unnamed 193: U38#2.4; also elsewhere on the board
unnamed 194: U38#2.3; also elsewhere on the board
unnamed 195: U38#2.10; also elsewhere on the board
unnamed 196: U38#2.2; also elsewhere on the board
unnamed 197: U38#2.9; also elsewhere on the board
unnamed 198: U38#2.5; also elsewhere on the board
unnamed 199: U38#2.6; also elsewhere on the board
unnamed 201: U38#2.1; also elsewhere on the board
unnamed 202: U38#2.8; also elsewhere on the board

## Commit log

2026-04-25 Add project files
2026-05-01 Saving before I restart
2026-05-03 Adjustments
2026-06-11 Fixing old stuff
2026-06-12 Update a shit ton
